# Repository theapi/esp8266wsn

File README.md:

# esp8266WSN

ESP8266 Wireless Sensor Network 

## Transmitter
Soil moisture sensors that transmit their data to the ESPNOW network.

- [Hardware](./transmitter/hardware)
- [Schematic](./transmitter/hardware/transmitter.pdf)
- [Software](./transmitter/software)

## Receiver
The receiver for the ESPNOW network, which sends the data to the network bridge.

- [Hardware](./receiver/hardware)
- [Software](./receiver/sfotware)

## Network Bridge
Connects the ESPNOW network to the WiFi network.

- [Software](./network_bridge)

## Monitor
Very basic UDP message listeners are provided in this repo:

- [C](./monitor/c)
- [php](./monitor/php)

A more sophisticated monitor is the [WSN Monitor](https://gitlab.com/theapi/wsn_monitor_sdl)

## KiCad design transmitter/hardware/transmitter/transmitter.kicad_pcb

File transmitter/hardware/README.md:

# Transmitter Hardware

[Schematic](./transmitter.pdf)

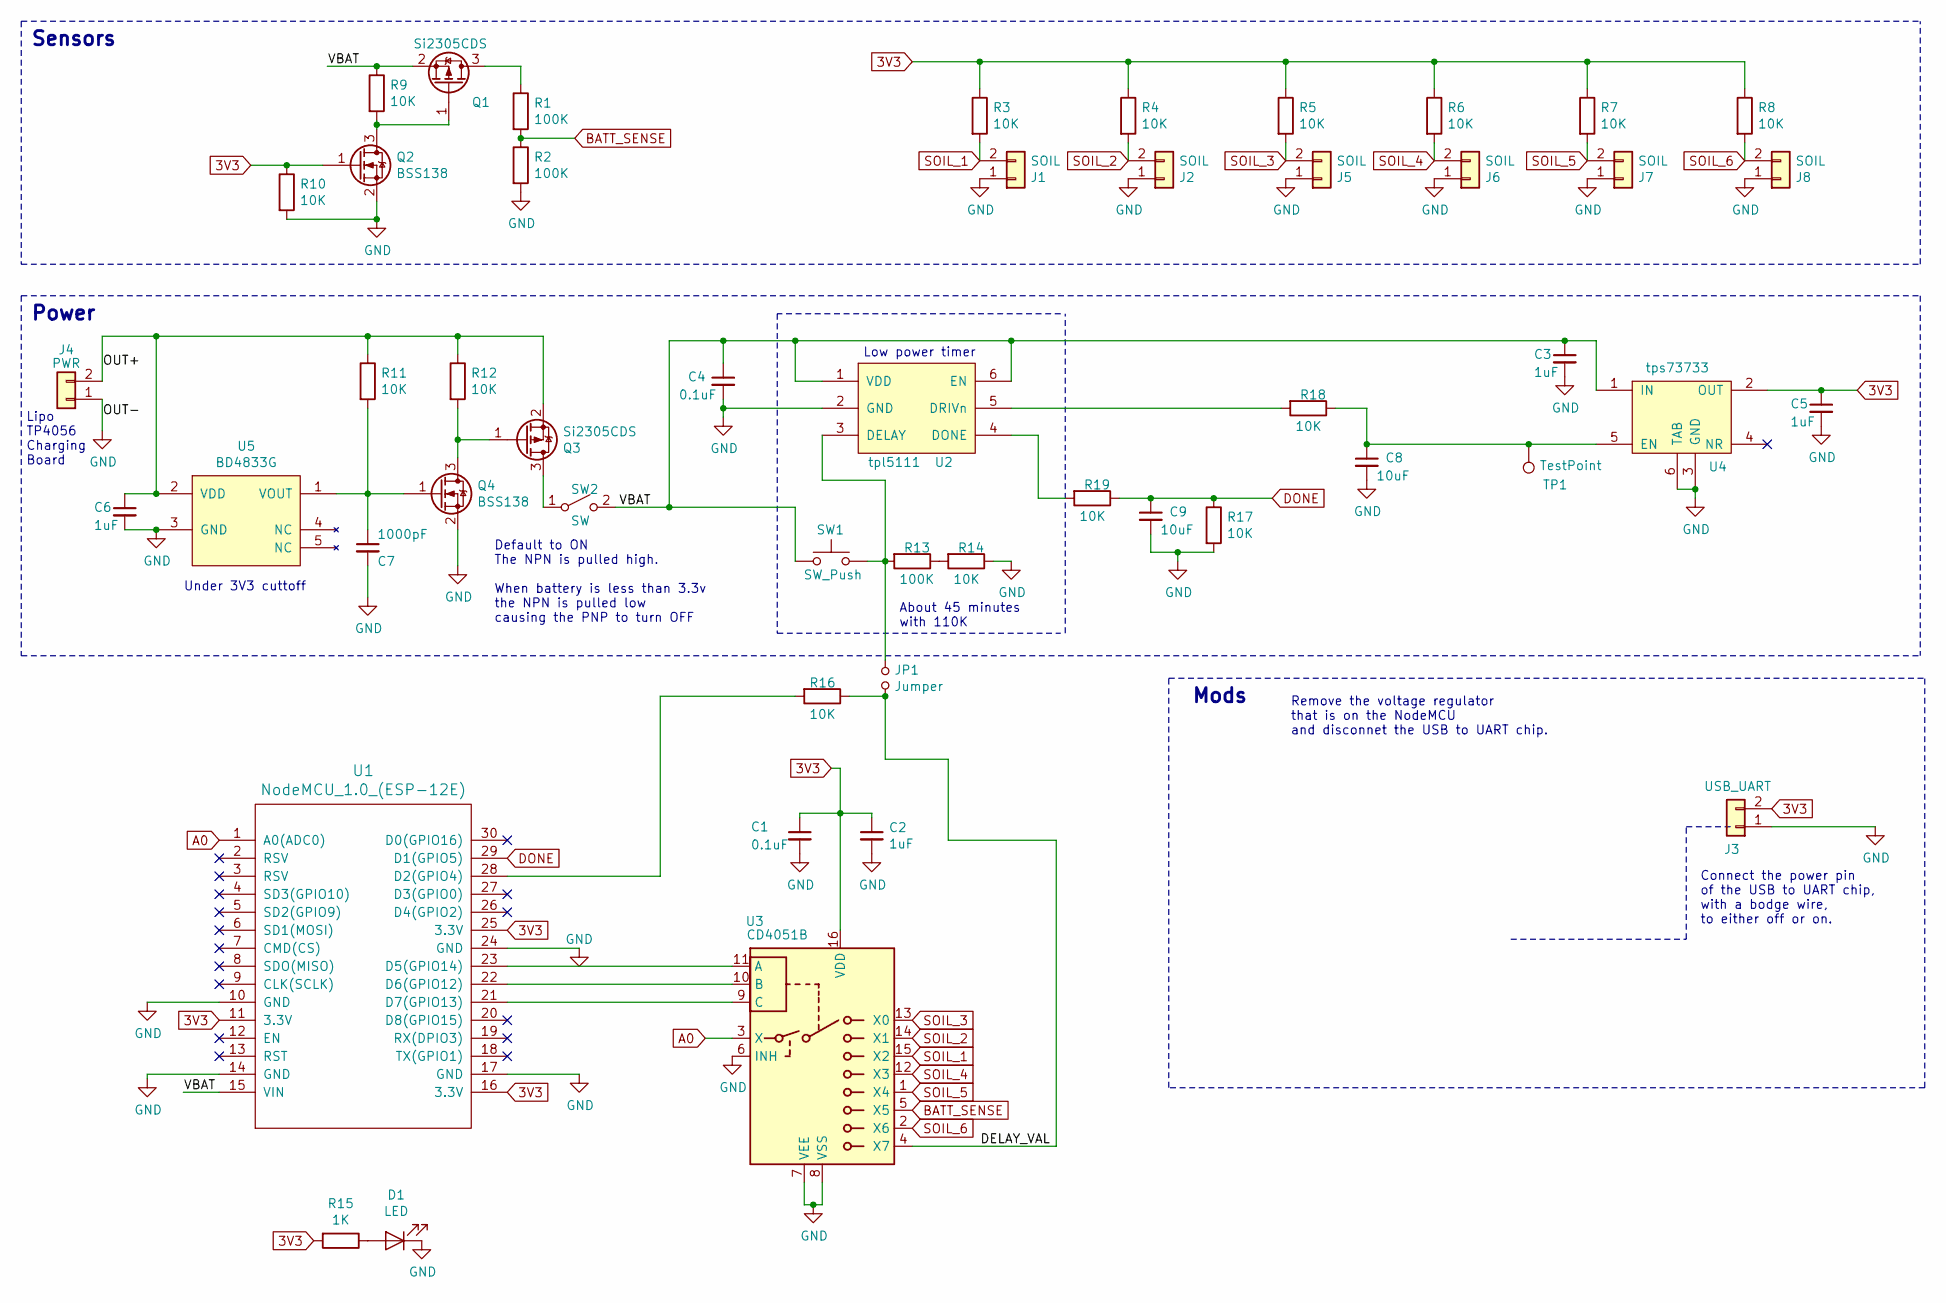
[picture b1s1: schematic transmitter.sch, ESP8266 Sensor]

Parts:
C1, C4: 0.1uF; C_0603_1608Metric_Pad1.05x0.95mm_HandSolder
C2, C3, C5, C6: 1uF; C_0603_1608Metric_Pad1.05x0.95mm_HandSolder
C7: 1000pF; C_0603_1608Metric_Pad1.05x0.95mm_HandSolder
C8, C9: 10uF; C_0603_1608Metric_Pad1.05x0.95mm_HandSolder
D1: LED; LED_0805_2012Metric_Pad1.15x1.40mm_HandSolder
J1, J2, J5, J6, J7, J8: SOIL; JST_XH_B02B-XH-A_1x02_P2.50mm_Vertical
J3: USB_UART; PinHeader_1x02_P2.54mm_Vertical
J4: PWR; tp4056
JP1: Jumper; SolderJumper-2_P1.3mm_Open_RoundedPad1.0x1.5mm
Q1, Q3: Si2305CDS; SOT-23
Q2, Q4: BSS138; SOT-23
R1, R2, R13: 100K; R_0603_1608Metric_Pad1.05x0.95mm_HandSolder
R3, R4, R5, R6, R7, R8, R9, R10, R11, R12, R14, R16, R17, R18, R19: 10K; R_0603_1608Metric_Pad1.05x0.95mm_HandSolder
R15: 1K; R_0603_1608Metric_Pad1.05x0.95mm_HandSolder
SW1: SW_Push; SW_Tactile_Straight_KSL0Axx1LFTR
SW2: SW; PinHeader_1x02_P2.54mm_Vertical
TP1: TestPoint; TestPoint_Pad_D1.0mm
U1: NodeMCU_1.0_(ESP-12E); NodeMCU1.0(12-E)
U2: tpl5111; SOT-6-DDC
U3: CD4051B; SOIC-16_3.9x9.9mm_P1.27mm
U4: tps73733; SOT-223-6
U5: BD4833G; SOT-23-5_HandSoldering

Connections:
3V3: C1.1, C2.1, C5.1, J3.2, Q2.1 (G), R3.1, R4.1, R5.1, R6.1, R7.1, R8.1, R10.1, R15.2, U1.11 (3.3V), U1.16 (3.3V), U1.25 (3.3V), U3.16 (VDD), U4.2 (OUT)
/DELAY_VAL: JP1.1, R16.1, U3.4 (X7)
/OUT+: C6.1, J4.2, Q3.2 (S), R11.1, R12.1, U5.2 (VDD)
/VBAT: C3.1, C4.1, Q1.2 (S), R9.1, SW1.1, SW2.2 (B), U1.15 (VIN), U2.1 (VDD), U2.6 (EN), U4.1 (IN)
A0: U1.1 (A0(ADC0)), U3.3 (X)
BATT_SENSE: R1.2, R2.1, U3.5 (X5); also elsewhere on the board
DONE: C9.1, R17.1, R19.1, U1.29 (D1(GPIO5))
GND: C1.2, C2.2, C3.2, C4.2, C5.2, C6.2, C7.2, C8.2, C9.2, D1.1 (K), J1.1, J2.1, J3.1, J4.1, J5.1, J6.1, J7.1, J8.1, Q2.2 (S), Q4.2 (S), R2.2, R10.2, R14.1, R17.2, U1.10 (GND), U1.14 (GND), U1.17 (GND), U1.24 (GND), U2.2 (GND), U3.6 (INH), U3.7 (VEE), U3.8 (VSS), U4.3 (GND), U4.6 (TAB), U5.3 (GND)
unnamed: C7.1, Q4.1 (G), R11.2, U5.1 (VOUT)
unnamed: C8.1, R18.1, TP1.1, U4.5 (EN)
unnamed: D1.2 (A), R15.1
unnamed: JP1.2, R13.2, SW1.2, U2.3 (DELAY)
unnamed: Q1.1 (G), Q2.3 (D), R9.2
unnamed: Q1.3 (D), R1.1
unnamed: Q3.1 (G), Q4.3 (D), R12.2
unnamed: Q3.3 (D), SW2.1 (A)
unnamed: R13.1, R14.2
unnamed: R16.2, U1.28 (D2(GPIO4))
unnamed: R18.2, U2.5 (DRIVn)
unnamed: R19.2, U2.4 (DONE)
unnamed: U1.21 (D7(GPIO13)), U3.9 (C)
unnamed: U1.22 (D6(GPIO12)), U3.10 (B)
unnamed: U1.23 (D5(GPIO14)), U3.11 (A)
SOIL_1: J1.2, R3.2, U3.15 (X2)
SOIL_2: J2.2, R4.2, U3.14 (X1)
SOIL_3: J5.2, R5.2, U3.13 (X0)
SOIL_4: J6.2, R6.2, U3.12 (X3)
SOIL_5: J7.2, R7.2, U3.1 (X4)
SOIL_6: J8.2, R8.2, U3.2 (X6)

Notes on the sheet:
Remove the voltage regulator that is on the NodeMCU and disconnet the USB to UART chip.
Connect the power pin of the USB to UART chip, with a bodge wire, to either off or on.
Power
Sensors
Mods
Lipo TP4056 Charging Board
Default to ON The NPN is pulled high. When battery is less than 3.3v the NPN is pulled low causing the PNP to turn OFF
About 45 minutes with 110K
Low power timer
Under 3V3 cuttoff

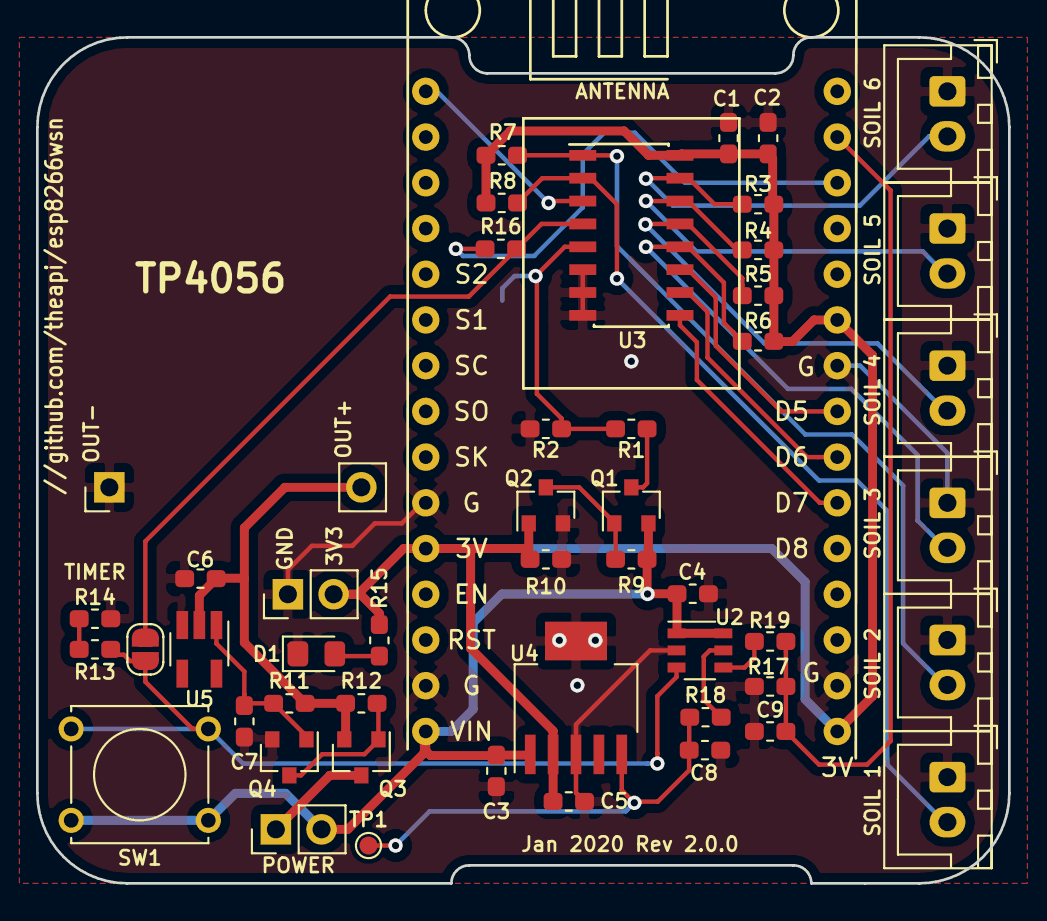
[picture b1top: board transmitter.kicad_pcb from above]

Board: 2 copper layers, 54.0 x 47.0 mm, 51 parts (1 on the bottom side), 29 nets.

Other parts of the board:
TP2: TestPoint; TestPoint_Pad_D1.0mm

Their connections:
BATT_SENSE: TP2.1; also elsewhere on the board

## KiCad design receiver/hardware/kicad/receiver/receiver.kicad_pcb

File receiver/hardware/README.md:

# Hardware

- [Schematic](./kicad/receiver/receiver.pdf)
- [Datasheets](./datasheets)

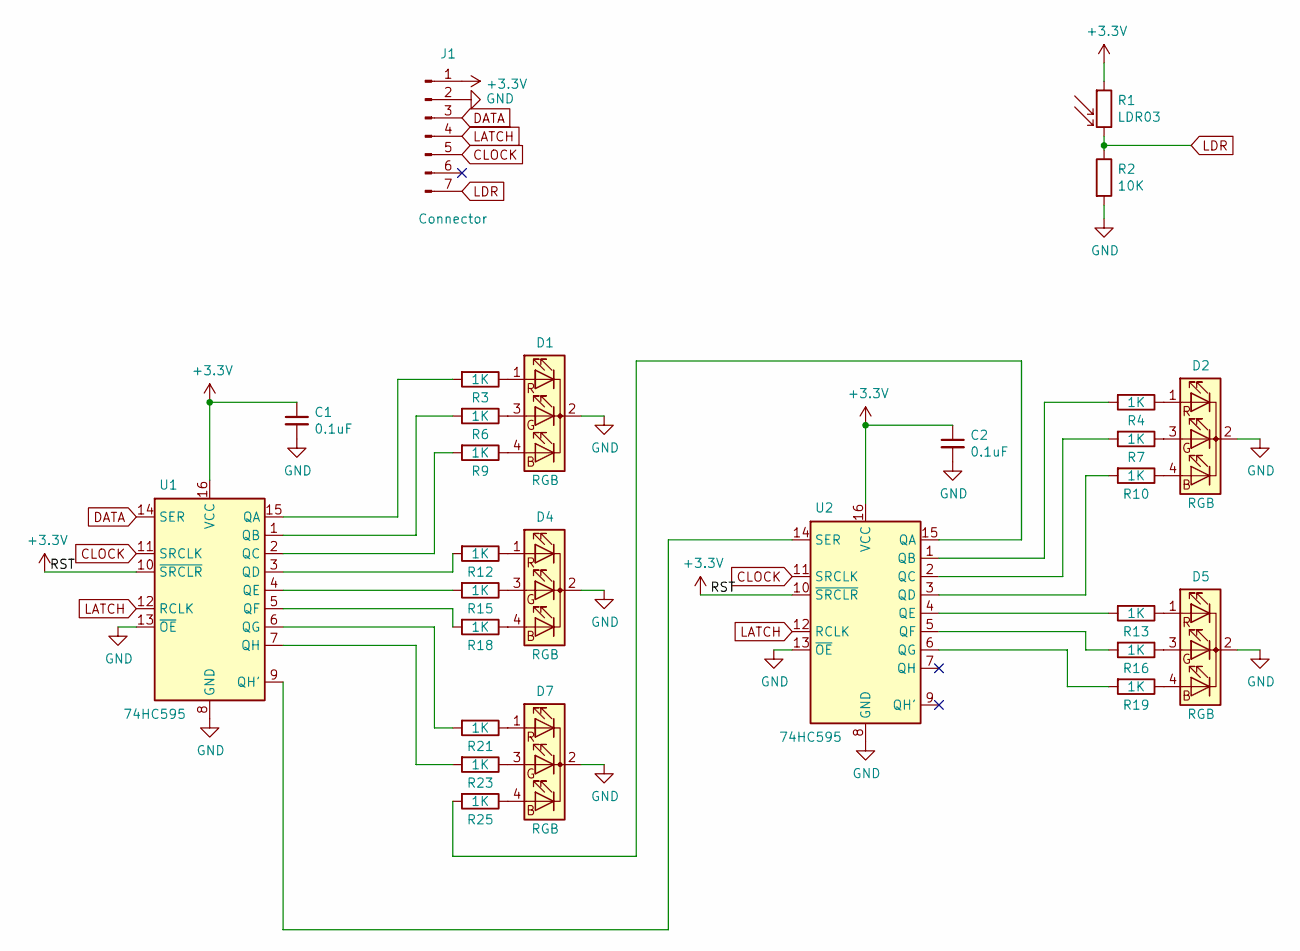
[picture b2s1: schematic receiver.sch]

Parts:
C1, C2: 0.1uF; C_0603_1608Metric_Pad1.05x0.95mm_HandSolder
D1, D2, D4, D5, D7: RGB; LED_D5.0mm-4_RGB
J1: Connector; PinHeader_1x07_P2.54mm_Horizontal
R1: LDR03; R_LDR_5.1x4.3mm_P3.4mm_Vertical
R2: 10K; R_0603_1608Metric_Pad1.05x0.95mm_HandSolder
R3, R4, R6, R7, R9, R10, R12, R13, R15, R16, R18, R19, R21, R23, R25: 1K; R_0603_1608Metric_Pad1.05x0.95mm_HandSolder
U1, U2: 74HC595; TSSOP-16_4.4x5mm_P0.65mm

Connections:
+3V3: C1.1, C2.1, J1.1, R1.1, U1.10 (~SRCLR), U1.16 (VCC), U2.10 (~SRCLR), U2.16 (VCC)
CLOCK: J1.5, U1.11 (SRCLK), U2.11 (SRCLK)
DATA: J1.3, U1.14 (SER)
GND: C1.2, C2.2, D1.2 (K), D2.2 (K), D4.2 (K), D5.2 (K), D7.2 (K), J1.2, R2.2, U1.8 (GND), U1.13 (~OE), U2.8 (GND), U2.13 (~OE)
LATCH: J1.4, U1.12 (RCLK), U2.12 (RCLK)
LDR: J1.7, R1.2, R2.1
unnamed: D1.1 (RA), R3.1
unnamed: D1.3 (GA), R6.1
unnamed: D1.4 (BA), R9.1
unnamed: D2.1 (RA), R4.1
unnamed: D2.3 (GA), R7.1
unnamed: D2.4 (BA), R10.1
unnamed: D4.1 (RA), R12.1
unnamed: D4.3 (GA), R15.1
unnamed: D4.4 (BA), R18.1
unnamed: D5.1 (RA), R13.1
unnamed: D5.3 (GA), R16.1
unnamed: D5.4 (BA), R19.1
unnamed: D7.1 (RA), R21.1
unnamed: D7.3 (GA), R23.1
unnamed: D7.4 (BA), R25.1
unnamed: R3.2, U1.15 (QA)
unnamed: R4.2, U2.1 (QB)
unnamed: R6.2, U1.1 (QB)
unnamed: R7.2, U2.2 (QC)
unnamed: R9.2, U1.2 (QC)
unnamed: R10.2, U2.3 (QD)
unnamed: R12.2, U1.3 (QD)
unnamed: R13.2, U2.4 (QE)
unnamed: R15.2, U1.4 (QE)
unnamed: R16.2, U2.5 (QF)
unnamed: R18.2, U1.5 (QF)
unnamed: R19.2, U2.6 (QG)
unnamed: R21.2, U1.6 (QG)
unnamed: R23.2, U1.7 (QH)
unnamed: R25.2, U2.15 (QA)
unnamed: U1.9 (QH'), U2.14 (SER)

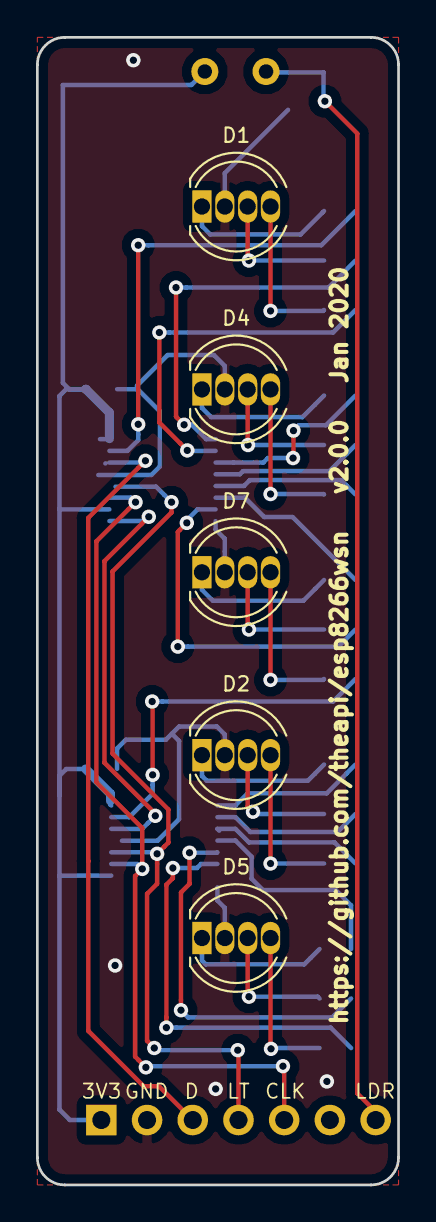
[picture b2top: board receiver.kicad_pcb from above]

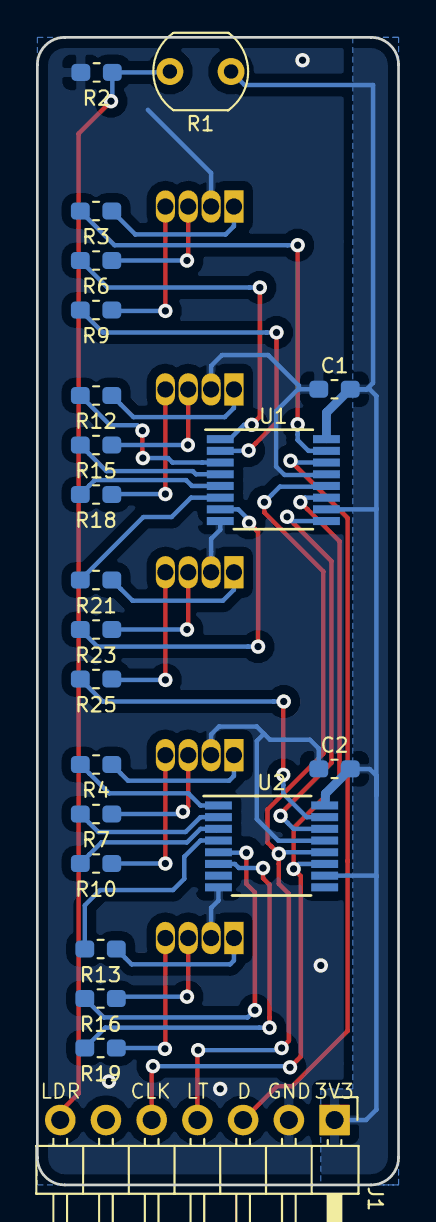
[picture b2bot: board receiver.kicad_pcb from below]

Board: 2 copper layers, 20.1 x 63.8 mm, 27 parts (22 on the bottom side), 37 nets.

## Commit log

2019-10-05 Start of independant display on & off
2019-10-06 Start of display lib
2019-10-06 Priority
2019-10-07 DISPLAY_HandleTypeDef for controlling the display
2019-10-08 Instant off/on
2019-10-08 Clean up
2019-10-09 Listen for ESP Now messages
2019-10-10 Show the receive count
2019-10-19 Log the payload
2019-10-19 Transmitter with sensor payload
2019-10-20 Payload
2019-10-20 Pass payload to parser
2019-10-20 No need for an event loop handler
2019-10-20 Removed old code
2019-10-20 Light readings adjustment
2019-10-22 Restart on error
2019-10-22 Simpler sending
2019-10-22 No master key
2019-10-22 Use RAM for wifi data
2019-10-22 Config
2019-10-22 Removed unused headers
2019-10-22 Removed commented code
2019-10-22 Google code formatting style
2019-10-22 Removed NVS
2019-10-22 No need for event id
2019-10-22 Simpler code
2019-10-22 Fixed data size
2019-10-23 Moved network functions
2019-10-26 Moved espnow code
2019-10-26 Light sensor in its own file
2019-10-27 Changed function naming convention
2019-10-27 Message id
2019-10-27 ADC readings on the sensor
2019-10-27 Fixed typo
2019-10-30 Hardware device id
2019-11-01 Mac address instead of device id
2019-11-01 Message type
2019-11-01 Moved to software directory
2019-11-01 Analog multiplexer
2019-11-01 Allow full use of the multiplexer
2019-11-01 Schematic
2019-11-01 Sensors
2019-11-01 Initial PCB layaout
2019-11-01 Layout
2019-11-01 All connected
2019-11-01 Power traces
2019-11-02 Multiple soil sensors
2019-11-02 JST connectors
2019-11-03 Vin & battery straps
2019-11-03 battery straps
2019-11-03 TP4056
2019-11-04 Labels
2019-11-04 Moved the ldo
2019-11-04 nodemcu footprint
2019-11-04 Tweaks
2019-11-04 Silkscreen
2019-11-05 Alternate LDO
2019-11-05 Corrected the Nodemcu footprint
2019-11-05 Sunflowers
2019-11-10 Slect multiplexer channel
2019-11-10 Map hardware input to multiplexer channels
2019-11-10 Gerbers
2019-11-13 Battery calibration
2019-11-13 Sensor power pin & mapping to the labels
2019-11-13 Battery in mV
2019-11-19 Sleep again if the battery is too low
2019-11-23 Deep sleep
2019-11-23 Batt calibration
2019-12-01 UART out of the receiver
2019-12-01 Start of network bridge
2019-12-01 Common payload
2019-12-01 increment serialized buffer index
2019-12-01 Default serial output for ADC values
2019-12-08 Send serialized data
2019-12-08 Buffer size fix
2019-12-08 Payload agnostic bridge
2019-12-11 One led per sensor
2019-12-12 Cleaner pixel setting
2019-12-12 Clear a sensor's led if not heard from for a while.
2019-12-13 batt & delay in the payload
2019-12-13 UDP monitor in C
2019-12-13 Use the UDP server for this project
2019-12-13 Use the payload delay to decide how long to wait
2019-12-14 Mac address first in the payload
2019-12-14 Compare mac addresses as bytes
2019-12-14 Multiple sensors
2019-12-15 memcpy is not my friend
2019-12-15 Handle line buffer correctly
2019-12-24 Moved the delay field to after the mac
2019-12-24 Remove old sensors
2019-12-27 Payload type
2019-12-29 Corrected the delay time
2019-12-29 Use payload for the basic data
2019-12-30 Disabled initial battery check, to find cause of not waking after 10 seconds
2019-12-30 Start gpio after wifi
2019-12-31 GPIO setup first
2020-01-01 Lower power turn off
2020-01-06 External low power timer
2020-01-06 Low power
2020-01-08 Assigned footprints
2020-01-08 Start of placement
2020-01-08 Smaller multiplexer
2020-01-08 Wired multiplexer
2020-01-09 TPL5111 footprint
2020-01-09 Wired the low voltage cutoff
2020-01-11 Power led
2020-01-11 Wired
2020-01-11 Logos
2020-01-11 Renders
2020-01-11 External timer to remove power
2020-01-11 Add new file
2020-01-11 Swapped sensor polarity
2020-01-11 Graphic silkscreen
2020-01-12 Moved directory
2020-01-12 Receiver LED display
2020-01-12 Initial layout
2020-01-13 Resizing
2020-01-14 Fit beneath the NodeMCU
2020-01-15 PNGs
2020-01-15 Cropped images
2020-01-17 Timer resistors on the bottom
2020-01-17 Measure the delay time
2020-01-18 Optionally measure timer resistors
2020-01-18 Rotated timer IC
2020-01-21 tpl5111 layout tweak
2020-01-21 Fit within 70mm circle
2020-01-22 Filters on the timer lines
2020-01-27 Faster filter
2020-01-27 Platform IO
2020-02-16 Two shift registers
2020-02-17 5 sensors
2020-03-01 Battery calibration & timer delay
2020-03-15 LEDs dependendant on the ambiant light
2020-03-15 Calibration on the battery
